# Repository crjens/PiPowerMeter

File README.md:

PiPowerMeter
=====

PiPowerMeter is an energy usage monitor based on the Cirrus Logic CS5463/5490 energy IC's (http://www.cirrus.com/en/products/pro/detail/P1092.html) and a Raspberry Pi.  It consists of two custom designed stacking pcb's.  The control board houses the power supply, energy IC, voltage sensors and supporting electronics.  The input board houses 16 multiplexed current input channels that allow monitoring up to 16 different circuits via standard clamp-on ct's.  A single control board supports up to 8 stacked input boards for a total monitoring capacity of up to 128 circuits.
The system is controlled by a nodejs based program running on the Raspberry Pi and includes a self contained web based monitoring portal.  Energy data are stored locally on the Raspberry Pi in a sqlite database making the system 100% stand-alone with no requirement for additional hardware or external servers.

Features
--------
 - 100% stand alone system with no reliance on external hardware or servers
 - Ability to monitor up to 128 circuits via round-robin sampling
 - Uses simple off the shelf clamp-on current sensors
 - Highly accurate measurement of voltage, current, power usage and power factor based on CS5463/CS5490 energy IC
 - Raspberry Pi based control system
   * All data stored locally in sqlite database
   * Web based monitoring portal for viewing energy usage and configuration
   * Ability to receive text alerts for overloads or other events.

Screenshots
-----------
- [Main](https://raw.githubusercontent.com/crjens/PiPowerMeter/master/Documentation/main.png)
- [Daily](https://raw.githubusercontent.com/crjens/PiPowerMeter/master/Documentation/graph.png)
- [Instantaneous](https://raw.githubusercontent.com/crjens/PiPowerMeter/master/Documentation/instant.png)
- [Readings](https://raw.githubusercontent.com/crjens/PiPowerMeter/master/Documentation/readings.png)
- [Configuration](https://raw.githubusercontent.com/crjens/PiPowerMeter/master/Documentation/config.png)

Additional Images
-----------------
- [Installed System](https://raw.githubusercontent.com/crjens/PiPowerMeter/master/Documentation/DSC_0077.JPG)
- [Installed System 2](https://raw.githubusercontent.com/crjens/PiPowerMeter/master/Documentation/DSC_0078.JPG)
- [Sensors](https://raw.githubusercontent.com/crjens/PiPowerMeter/master/Documentation/DSC_0002.JPG)
- [Boards](https://raw.githubusercontent.com/crjens/PiPowerMeter/master/Documentation/DSC_0012.JPG)

Hardware Installation
---------------------
1. The Raspberry Pi mounts directly to the 40-pin header on the control board and is powered from the control board's universal power supply.  Do not attempt to power the Raspberry Pi via its micro usb port or it may be damaged.
2. The control board requires a direct connection to the AC power source that is being monitored.  This AC connection provides both the voltage reference for the energy calculations as well as the power source for the Raspberry Pi and supporting electronics.  The AC power source is connected via 5 pin terminal connector shown [here](https://raw.githubusercontent.com/crjens/PiPowerMeter/master/Documentation/ACIn.jpg) and supports 100-240VAC and 50/60Hz.  

	- For US 120/240V split phase connect Ground, Neutral, AC1 and AC2.
	- For 240V single phase connect Ground, Neutral and AC1.
	- For 3 phase connect Ground, Neutral, AC1, AC2 and AC3.
3. Current sensors are connected to the input board via standard 3.5mm (1/8") audio plugs.  They must be current-type sensors without built-in sense resistors and must produce a full scale output of less than 50mA.  YHDC produces a full line of split-core current sensors that are easy to use, inexpensive and readily available [online](https://www.ebay.com/sch/i.html?_from=R40&_trksid=m570.l1313&_nkw=yhdc+sct013+sct006+sct019&_sacat=0&LH_TitleDesc=0&_osacat=0&_odkw=yhdc+sct013+sctoo0+sct019&LH_TitleDesc=0). Popular models include:
	- [YHDC-006 (20A)](http://en.yhdc.com/product1311.html?productId=612)
	- [YHDC-013-000 (100A)](http://en.yhdc.com/product1311.html?productId=401)
	- [YHDC-019 (200A)](http://en.yhdc.com/product1311.html?productId=380)
4. Connect the current sensors so that the current polarity reads correctly, (+) for circuits that consume energy and (-) for circuits that produce energy.  Connecting a sensor backwards will not harm anything so if you're not sure which way it should face just pick a direction and then reverse it if the readings are opposite of what you expect. 
	- Current sensors measure the sum of the current passing through them so they should normally be connected to a single conductor.  If connected to a multi-conductor cable, the current flowing in the line and neutral conductors will cancel each other and the sensor will read zero current.
	- YHDC sensors connected to line conductors should be oriented so that the printing on the face of the sensor faces toward the source (there's also an arrow on most sensors that should point toward the source).  If the sensor is connected to the neutral the direction should be reversed.  
5. Once the sensors are installed you'll need to configure the software to enable them.  This is done in the configuration page by adding a new circuit for each sensor and setting the sensor type, board, circuit and voltage reference.
	- There are several preconfigured types for common YHDC sensors and you can add additional types under the configuration tab.  When creating new sensor types set the scale value to 0.05 * the turns ratio of the sensor.  (YHDC SCT-013 has a turns ratio of 2000:1 so scale factor is 0.05*2000=100)
	- Board should be set to the id of the current board that the sensor is plugged into (0-7).
	- Channel should be set to the id that the sensor is plugged into (0-15).
	- Set Voltage to the voltage reference for the circuit.  If you aren't sure you can take a look at the current and voltage waveforms on the circuit page and experiment until you find the voltage reference that most closely matches the phase of the current waveform.
	- SampleTime sets the amount of time in seconds that the input current and voltage are sampled for each calculation.  Decreasing the SampleTime allows faster sampling but may adversly affect the accuracy of the calculations.  Valid values are between 0.05 and 60 seconds.  
	- Incorrect software settings won't cause any damage so you can experiment until you get them right.

Software Installation
---------------------
1. Any of the full size Raspberry Pi models with the 40 pin header are supported including: V1 A+, V1 B+, V2, V3 B, V3 B+ and V4 B.  The additional memory and computing power of the V2/V3/V4 models is recommended.
2. Start with latest Raspbian image from https://www.raspberrypi.org/software/operating-systems/
	1. (verified with Raspberry PI OS Lite 2021-03-04)
	2. It's recommended that you use the Lite version because it's smaller and installs faster but you can use either.
3. login to Pi with Putty or other ssh client
	1. the latest versions of Raspbian have ssh disabled.  You can enable ssh via raspi-config or just create an empty file named 'ssh' in the boot partition of the sd card.
4. Install the PiPowerMeter software by running the following command (you must install with root privileges such as the built-in pi account):
	1. wget -O - https://raw.githubusercontent.com/crjens/PiPowerMeter/master/setup.sh | bash
5. run 'sudo raspi-config' 
	1. set locale and timezone under Localisation options
	2. expand filesystem under Advanced options
	3. change user password (optional)
	4. reboot when prompted after exiting raspi-config
6. Open your browser to http://<Your Raspberry Pi's IP Address>:3000

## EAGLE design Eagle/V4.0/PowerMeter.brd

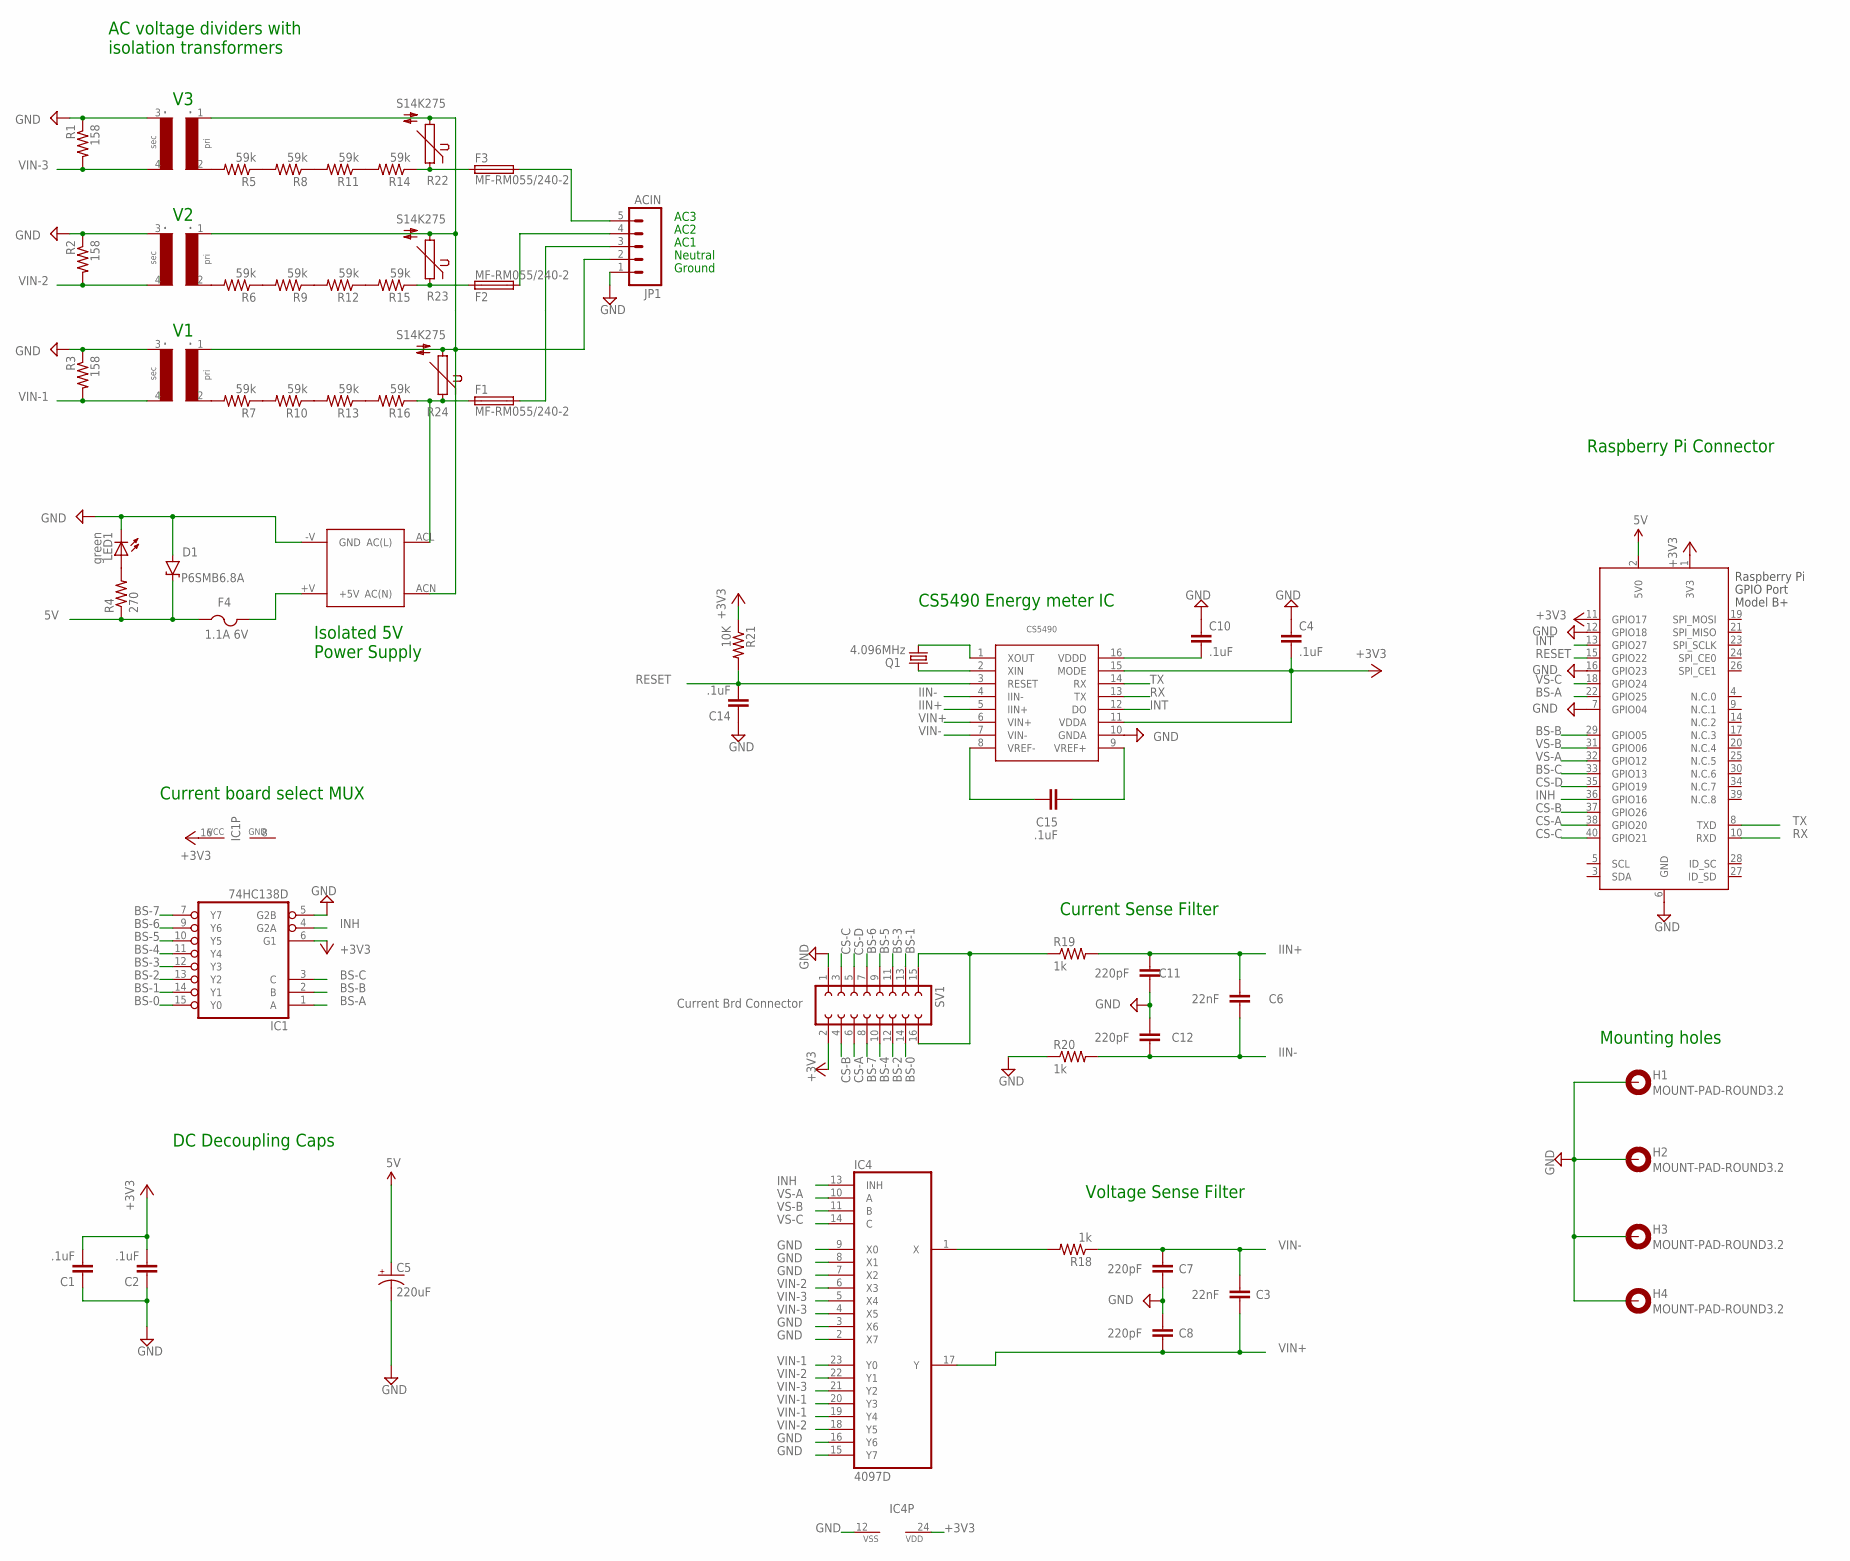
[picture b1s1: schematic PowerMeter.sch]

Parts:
C1, C2, C4, C10, C14, C15: .1uF; C1206; PARTNO C1206C104K5RAC7867
C3, C6: 22nF; C1206; PARTNO C1206C221J5GACTU
C5: 220uF; PANASONIC_D; PARTNO ESH227M016AE3AA
C7, C8, C11, C12: 220pF; C1206; PARTNO C1206C221J5GACTU
CS5490: CS5490; SOIC127P600X175-16N
D1: P6SMB6.8A; DO-214AA; PARTNO P6KE6.8A
F1, F2, F3: MF-RM055/240-2; TE5; PARTNO MF-RM055/240-2
F4: 1.1A 6V; 1812; PARTNO 0ZCC0110AF2C
H1, H2, H3, H4: MOUNT-PAD-ROUND3.2; 3,2-PAD
IC1: 74HC138D; SO16; PARTNO SN74HC138NSR
IC4: 4097D; SO24W
JP1: ACIN; SCREWTERMINAL-5MM-5; PARTNO 1935190
LED1: green; LED_1206; PARTNO LTST-C150GKT
Q1: 4.096MHz; HC49UP; PARTNO 9B-4.096MBBK-B
R1, R2, R3: 158; R1206; PARTNO RC1206FR-07158RL
R4: 270; R1206; PARTNO RC1206FR-07270RL
R5, R6, R7, R8, R9, R10, R11, R12, R13, R14, R15, R16: 59k; R1206; PARTNO RC1206FR-071KL
R18, R19, R20: 1k; R1206; PARTNO RC1206FR-071KL
R21: 10K; R1206; PARTNO RC1206FR-0710KL
R22, R23, R24: S14K275
SV1: Current Brd Connector; FE08-2; PARTNO PPTC082LFBN-RC
T1, T2, T3: TV16E
U$1: IRM-10
X1: RASPI_BOARD_B+_E4; RASPI_BOARD_B+_EDGES_4DRILL; PARTNO M20-9762046

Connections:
5V: C5.+, D1.C, F4.1, R4.1, X1.2 (5V0)
+3V3: C1.2, C2.2, C4.2, CS5490.11 (VDDA), CS5490.15 (MODE), IC1.6 (G1), IC1.16 (VCC), IC4.24 (VDD), R21.1, SV1.2, X1.1 (3V3), X1.11 (GPIO17)
+5V: F4.2, U$1.+V (+5V)
AC(L): F1.1, R16.1, R24.1, U$1.ACL (AC(L))
AC(N): JP1.2 (4), R22.2, R23.2, R24.2, T1.1, T2.1, T3.1, U$1.ACN (AC(N))
BS-0: IC1.15 (Y0), SV1.14
BS-1: IC1.14 (Y1), SV1.13
BS-2: IC1.13 (Y2), SV1.12
BS-3: IC1.12 (Y3), SV1.11
BS-4: IC1.11 (Y4), SV1.10
BS-5: IC1.10 (Y5), SV1.9
BS-6: IC1.9 (Y6), SV1.7
BS-7: IC1.7 (Y7), SV1.8
BS-A: IC1.1 (A), X1.22 (GPIO25)
BS-B: IC1.2 (B), X1.29 (GPIO05)
BS-C: IC1.3 (C), X1.33 (GPIO13)
CS-A: SV1.6, X1.38 (GPIO20)
CS-B: SV1.4, X1.37 (GPIO26)
CS-C: SV1.3, X1.40 (GPIO21)
CS-D: SV1.5, X1.35 (GPIO19)
GND: C1.1, C2.1, C4.1, C5.-, C7.1, C8.2, C10.1, C11.1, C12.2, C14.1, CS5490.10 (GNDA), D1.A, H1.B3,2, H2.B3,2, H3.B3,2, H4.B3,2, IC1.5 (G2B), IC1.8 (GND), IC4.2 (X7), IC4.3 (X6), IC4.7 (X2), IC4.8 (X1), IC4.9 (X0), IC4.12 (VSS), IC4.15 (Y7), IC4.16 (Y6), JP1.1 (5), LED1.C, R1.1, R2.1, R3.1, R20.1, SV1.1, T1.3, T2.3, T3.3, U$1.-V (GND), X1.6 (GND), X1.7 (GPIO04), X1.12 (GPIO18), X1.16 (GPIO23)
IIN+: C6.2, C11.2, CS5490.5 (IIN+), R19.2
IIN-: C6.1, C12.1, CS5490.4 (IIN-), R20.2
INH: IC1.4 (G2A), IC4.13 (INH), X1.36 (GPIO16)
INT: CS5490.12 (DO), X1.13 (GPIO27)
unnamed: CS5490.2 (XIN), Q1.1
unnamed: F2.1, R15.1, R23.1
unnamed: R5.1, R8.2
unnamed: R8.1, R11.2
unnamed: F1.2, JP1.3
unnamed: R9.1, R12.2
unnamed: LED1.A, R4.2
unnamed: IC4.1 (X), R18.2
unnamed: F3.2, JP1.5 (1)
unnamed: R13.1, R16.2
unnamed: R7.2, T3.2
unnamed: CS5490.1 (XOUT), Q1.2
unnamed: R7.1, R10.2
unnamed: R10.1, R13.2
unnamed: R6.2, T2.2
unnamed: R6.1, R9.2
unnamed: C10.2, CS5490.16 (VDDD)
unnamed: R12.1, R15.2
unnamed: R5.2, T1.2
unnamed: R11.1, R14.2
unnamed: F3.1, R14.1, R22.1
unnamed: R19.1, SV1.15, SV1.16
unnamed: C15.1, CS5490.8 (VREF-)
unnamed: C15.2, CS5490.9 (VREF+)
unnamed: F2.2, JP1.4 (2)
RESET: C14.2, CS5490.3 (RESET), R21.2, X1.15 (GPIO22)
RX: CS5490.13 (TX), X1.10 (RXD)
TX: CS5490.14 (RX), X1.8 (TXD)
VIN+: C3.1, C8.1, CS5490.6 (VIN+), IC4.17 (Y)
VIN-: C3.2, C7.2, CS5490.7 (VIN-), R18.1
VIN-1: IC4.19 (Y4), IC4.20 (Y3), IC4.23 (Y0), R3.2, T3.4
VIN-2: IC4.6 (X3), IC4.18 (Y5), IC4.22 (Y1), R2.2, T2.4
VIN-3: IC4.4 (X5), IC4.5 (X4), IC4.21 (Y2), R1.2, T1.4
VS-A: IC4.10 (A), X1.32 (GPIO12)
VS-B: IC4.11 (B), X1.31 (GPIO06)
VS-C: IC4.14 (C), X1.18 (GPIO24)

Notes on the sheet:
AC voltage dividers with isolation transformers
Isolated 5V Power Supply
DC Decoupling Caps
Raspberry Pi Connector
CS5490 Energy meter IC
Voltage Sense Filter
Current Sense Filter
Current board select MUX
Mounting holes
AC1
AC2
AC3
Neutral
Ground

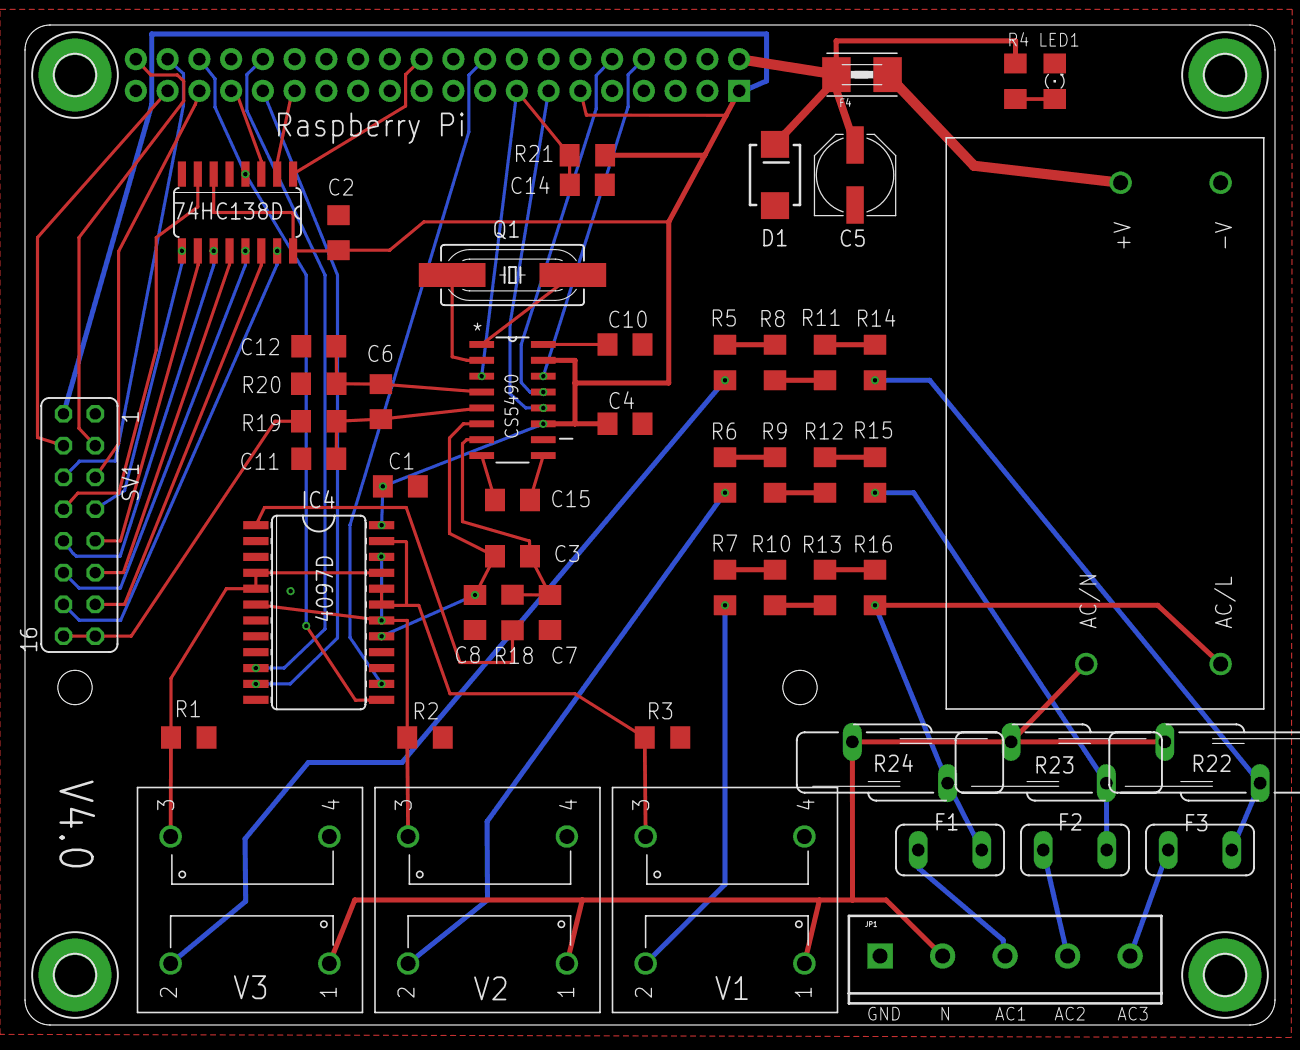
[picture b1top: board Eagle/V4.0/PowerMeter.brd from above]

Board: 2 copper layers, 100.0 x 80.0 mm, 57 parts (1 on the bottom side), 61 nets.

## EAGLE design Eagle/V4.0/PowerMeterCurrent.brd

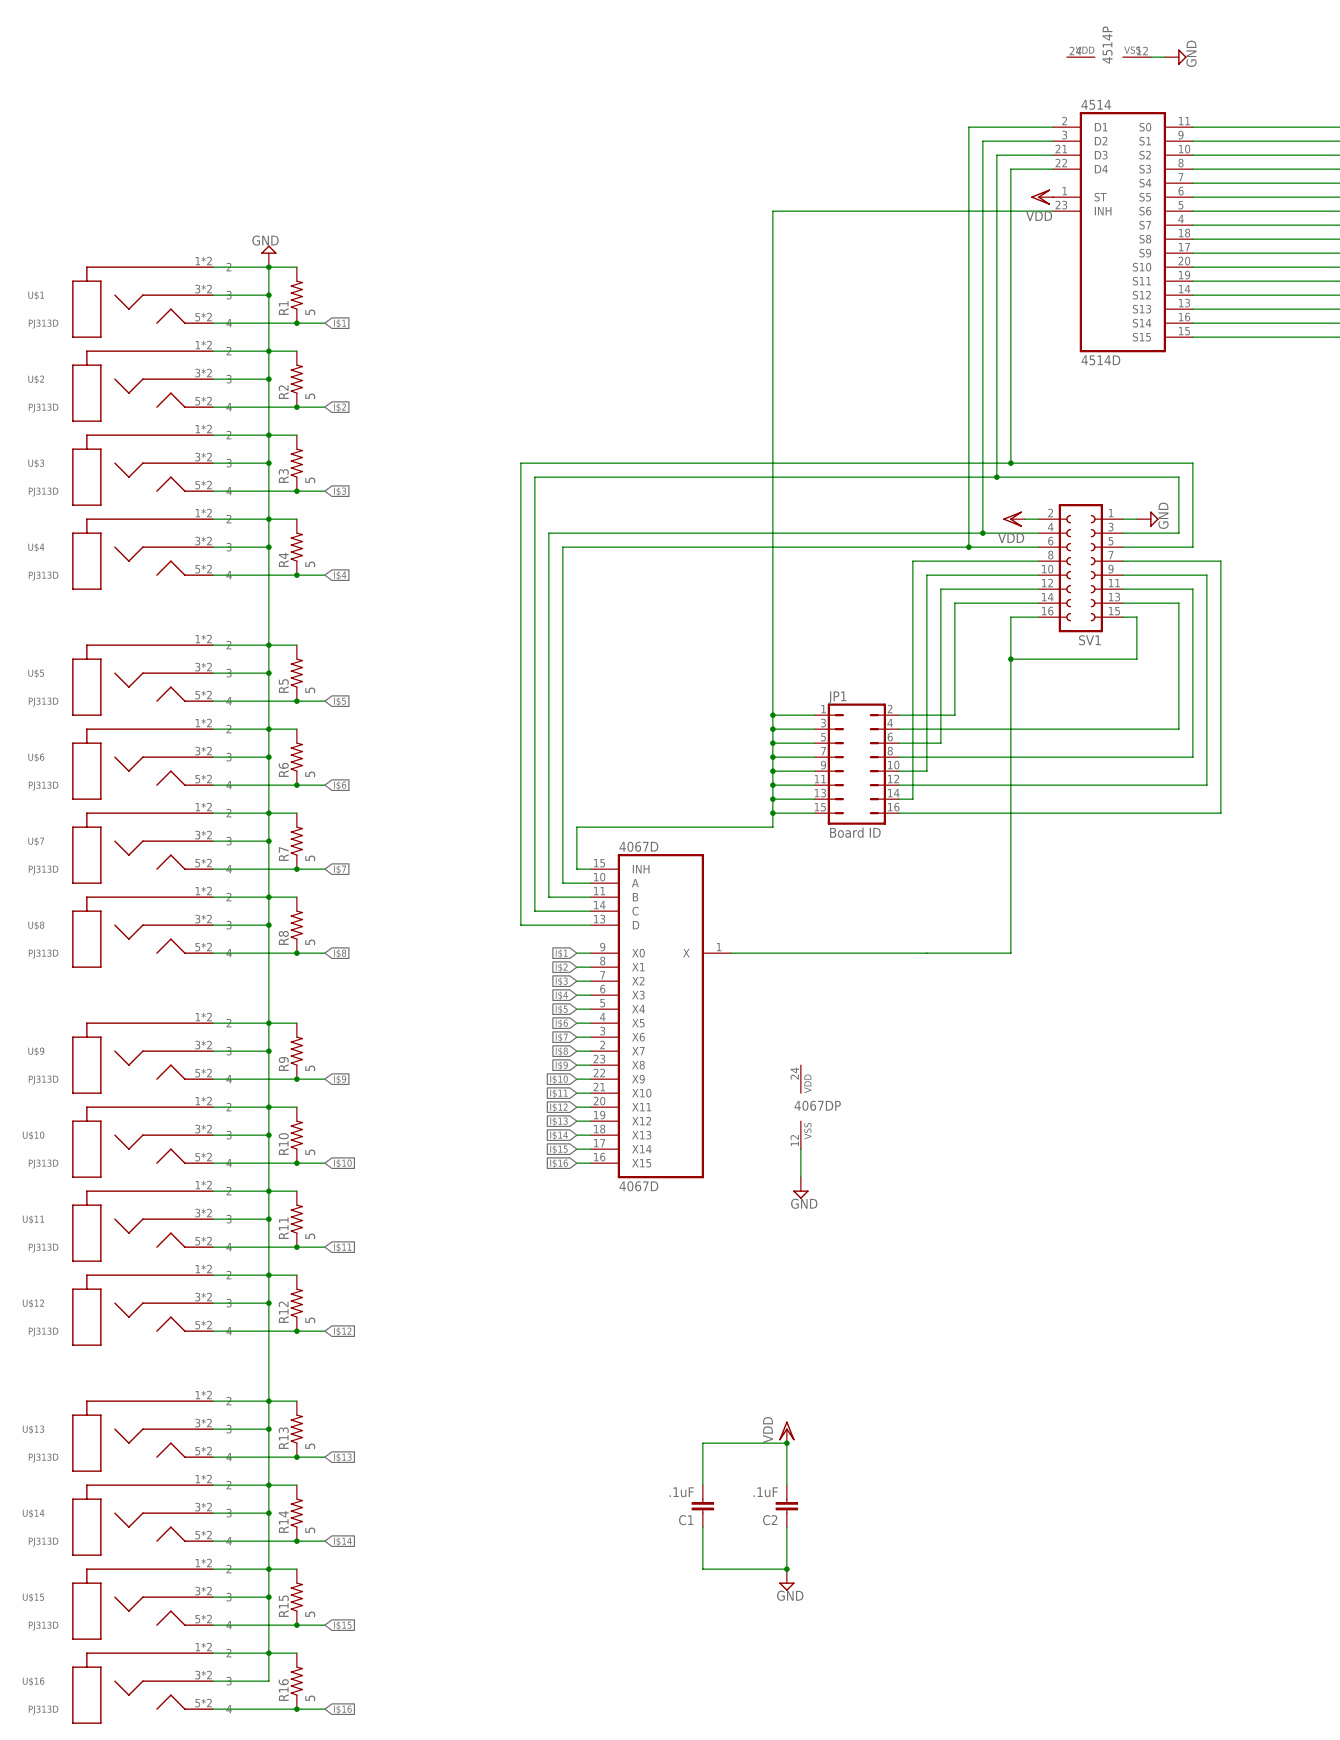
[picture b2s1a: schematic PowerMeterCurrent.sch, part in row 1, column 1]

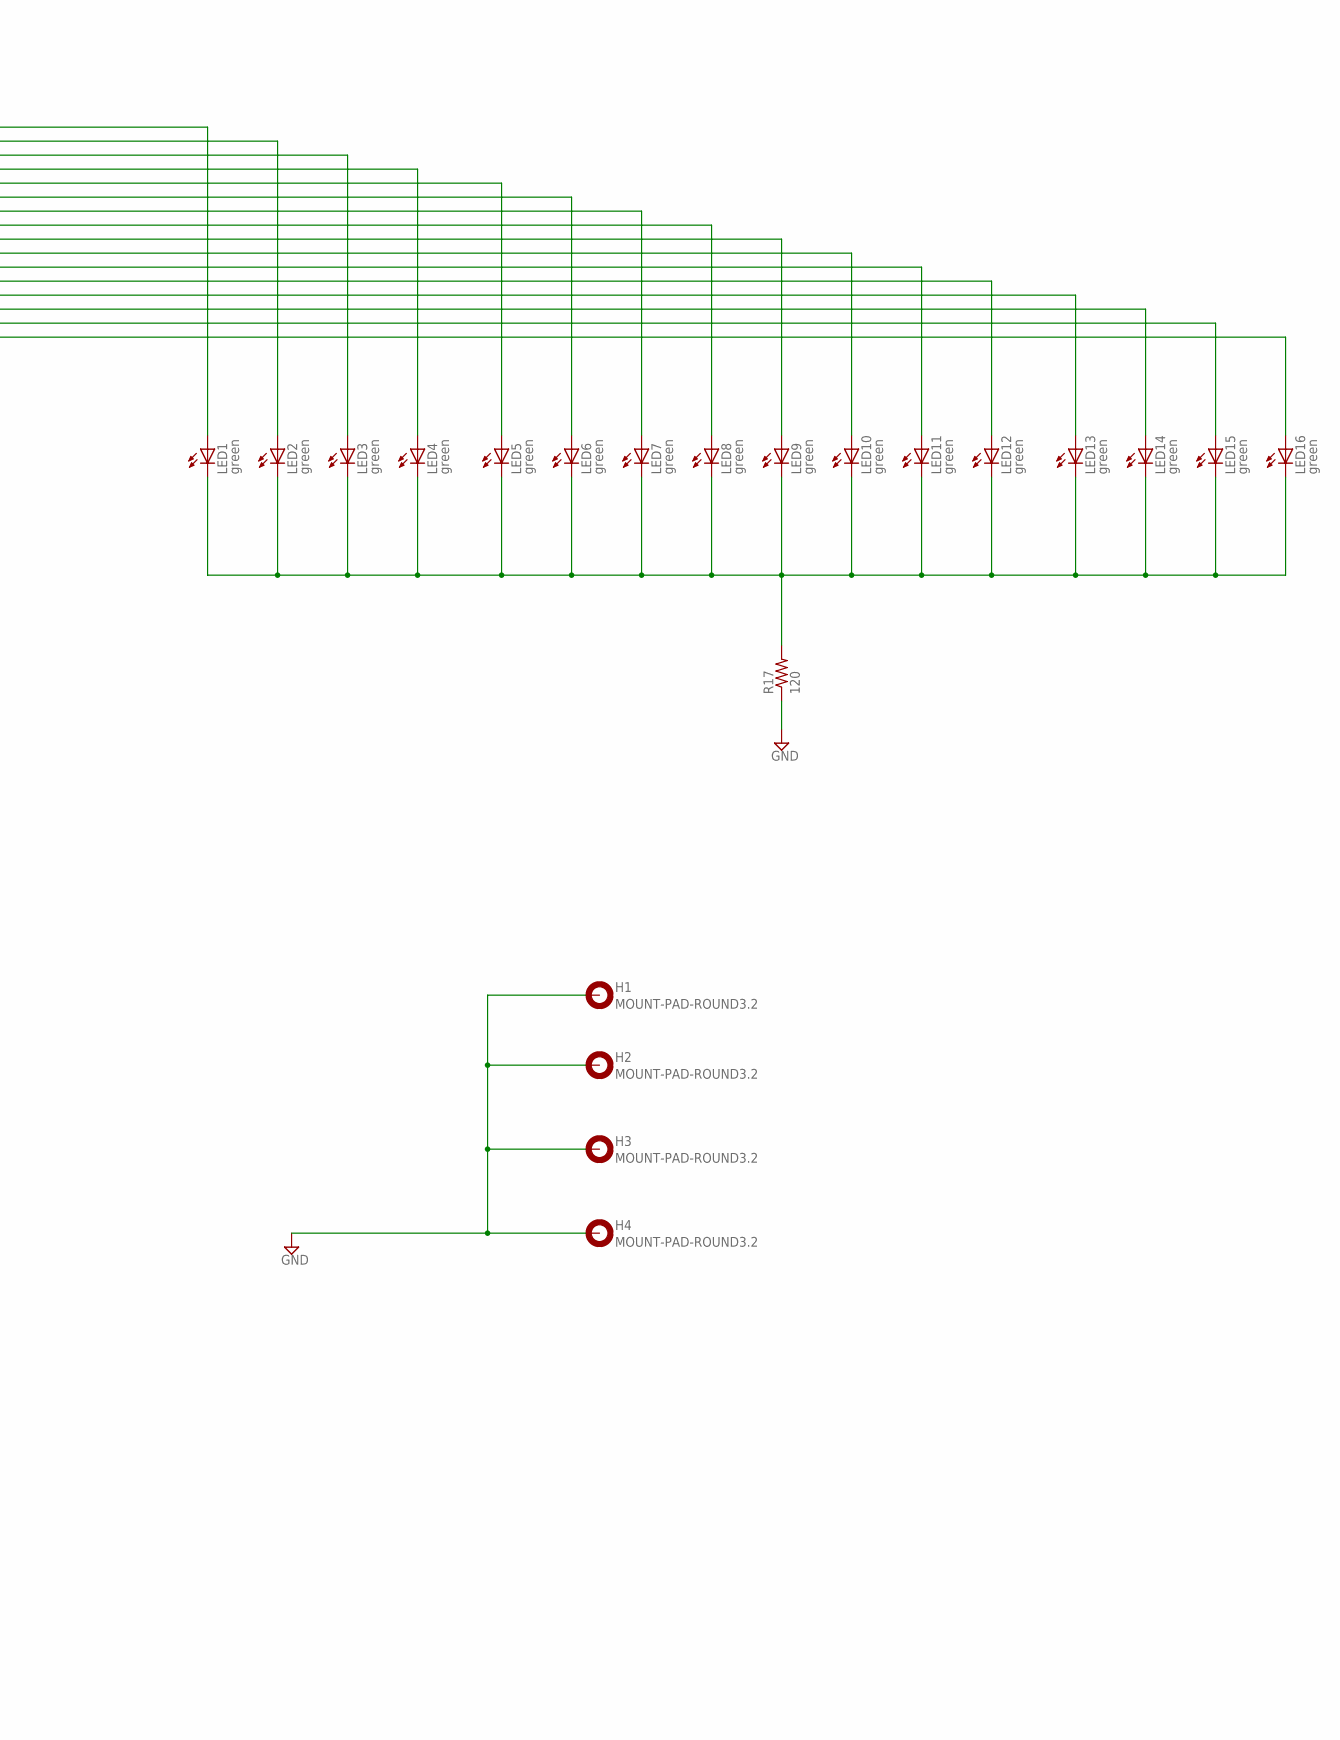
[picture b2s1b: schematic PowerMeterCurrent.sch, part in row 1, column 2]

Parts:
4067D: 4067D; SO24W; PARTNO 74HC4067D,652
4514: 4514D; SO24W; PARTNO 74HC154D,652
C1, C2: .1uF; C1206; PARTNO C1206C104K5RAC7867
H1, H2, H3, H4: MOUNT-PAD-ROUND3.2; 3,2-PAD
JP1: Board ID; JP8Q; PARTNO 67996-416HLF
LED1, LED2, LED3, LED4, LED5, LED6, LED7, LED8, LED9, LED10, LED11, LED12, LED13, LED14, LED15, LED16: green; LED_1206; PARTNO LTST-C150GKT
R1, R2, R3, R4, R5, R6, R7, R8, R9, R10, R11, R12, R13, R14, R15, R16: 5; R1206; PARTNO RC1206FR-077R5L
R17: 120; R1206; PARTNO RC1206FR-07120RL
SV1: FE08-2; PARTNO SSQ-108-02-T-D
U$1, U$2, U$3, U$4, U$5, U$6, U$7, U$8, U$9, U$10, U$11, U$12, U$13, U$14, U$15, U$16: PJ313D

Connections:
GND: 4067D.12 (VSS), 4514.12 (VSS), C1.1, C2.1, H1.B3,2, H2.B3,2, H3.B3,2, H4.B3,2, R1.2, R2.2, R3.2, R4.2, R5.2, R6.2, R7.2, R8.2, R9.2, R10.2, R11.2, R12.2, R13.2, R14.2, R15.2, R16.2, R17.1, SV1.1, U$1.1 (2), U$1.2, U$1.3, U$1.4 (3), U$2.1 (2), U$2.2, U$2.3, U$2.4 (3), U$3.1 (2), U$3.2, U$3.3, U$3.4 (3), U$4.1 (2), U$4.2, U$4.3, U$4.4 (3), U$5.1 (2), U$5.2, U$5.3, U$5.4 (3), U$6.1 (2), U$6.2, U$6.3, U$6.4 (3), U$7.1 (2), U$7.2, U$7.3, U$7.4 (3), U$8.1 (2), U$8.2, U$8.3, U$8.4 (3), U$9.1 (2), U$9.2, U$9.3, U$9.4 (3), U$10.1 (2), U$10.2, U$10.3, U$10.4 (3), U$11.1 (2), U$11.2, U$11.3, U$11.4 (3), U$12.1 (2), U$12.2, U$12.3, U$12.4 (3), U$13.1 (2), U$13.2, U$13.3, U$13.4 (3), U$14.1 (2), U$14.2, U$14.3, U$14.4 (3), U$15.1 (2), U$15.2, U$15.3, U$15.4 (3), U$16.1 (2), U$16.2, U$16.3, U$16.4 (3)
I$1: 4067D.9 (X0), R1.1, U$1.5 (4), U$1.6 (4)
I$2: 4067D.8 (X1), R2.1, U$2.5 (4), U$2.6 (4)
I$3: 4067D.7 (X2), R3.1, U$3.5 (4), U$3.6 (4)
I$4: 4067D.6 (X3), R4.1, U$4.5 (4), U$4.6 (4)
I$5: 4067D.5 (X4), R5.1, U$5.5 (4), U$5.6 (4)
I$6: 4067D.4 (X5), R6.1, U$6.5 (4), U$6.6 (4)
I$7: 4067D.3 (X6), R7.1, U$7.5 (4), U$7.6 (4)
I$8: 4067D.2 (X7), R8.1, U$8.5 (4), U$8.6 (4)
I$9: 4067D.23 (X8), R9.1, U$9.5 (4), U$9.6 (4)
I$10: 4067D.22 (X9), R10.1, U$10.5 (4), U$10.6 (4)
I$11: 4067D.21 (X10), R11.1, U$11.5 (4), U$11.6 (4)
I$12: 4067D.20 (X11), R12.1, U$12.5 (4), U$12.6 (4)
I$13: 4067D.19 (X12), R13.1, U$13.5 (4), U$13.6 (4)
I$14: 4067D.18 (X13), R14.1, U$14.5 (4), U$14.6 (4)
I$15: 4067D.17 (X14), R15.1, U$15.5 (4), U$15.6 (4)
I$16: 4067D.16 (X15), R16.1, U$16.5 (4), U$16.6 (4)
unnamed: 4067D.10 (A), 4514.2 (D1), SV1.6
unnamed: 4514.11 (S0), LED1.A
unnamed: 4067D.11 (B), 4514.3 (D2), SV1.4
unnamed: 4067D.14 (C), 4514.21 (D3), SV1.3
unnamed: 4067D.13 (D), 4514.22 (D4), SV1.5
unnamed: 4067D.15 (INH), 4514.23 (INH), JP1.1, JP1.3, JP1.5, JP1.7, JP1.9, JP1.11, JP1.13, JP1.15
unnamed: JP1.14, SV1.8
unnamed: JP1.10, SV1.10
unnamed: 4514.9 (S1), LED2.A
unnamed: JP1.6, SV1.12
unnamed: JP1.2, SV1.14
unnamed: 4067D.1 (X), SV1.15, SV1.16
unnamed: JP1.4, SV1.13
unnamed: JP1.8, SV1.11
unnamed: JP1.12, SV1.9
unnamed: JP1.16, SV1.7
unnamed: 4514.10 (S2), LED3.A
unnamed: LED1.C, LED2.C, LED3.C, LED4.C, LED5.C, LED6.C, LED7.C, LED8.C, LED9.C, LED10.C, LED11.C, LED12.C, LED13.C, LED14.C, LED15.C, LED16.C, R17.2
unnamed: 4514.8 (S3), LED4.A
unnamed: 4514.7 (S4), LED5.A
unnamed: 4514.6 (S5), LED6.A
unnamed: 4514.5 (S6), LED7.A
unnamed: 4514.4 (S7), LED8.A
unnamed: 4514.18 (S8), LED9.A
unnamed: 4514.17 (S9), LED10.A
unnamed: 4514.20 (S10), LED11.A
unnamed: 4514.19 (S11), LED12.A
unnamed: 4514.14 (S12), LED13.A
unnamed: 4514.13 (S13), LED14.A
unnamed: 4514.16 (S14), LED15.A
unnamed: 4514.15 (S15), LED16.A
VDD: 4067D.24 (VDD), 4514.1 (ST), 4514.24 (VDD), C1.2, C2.2, SV1.2

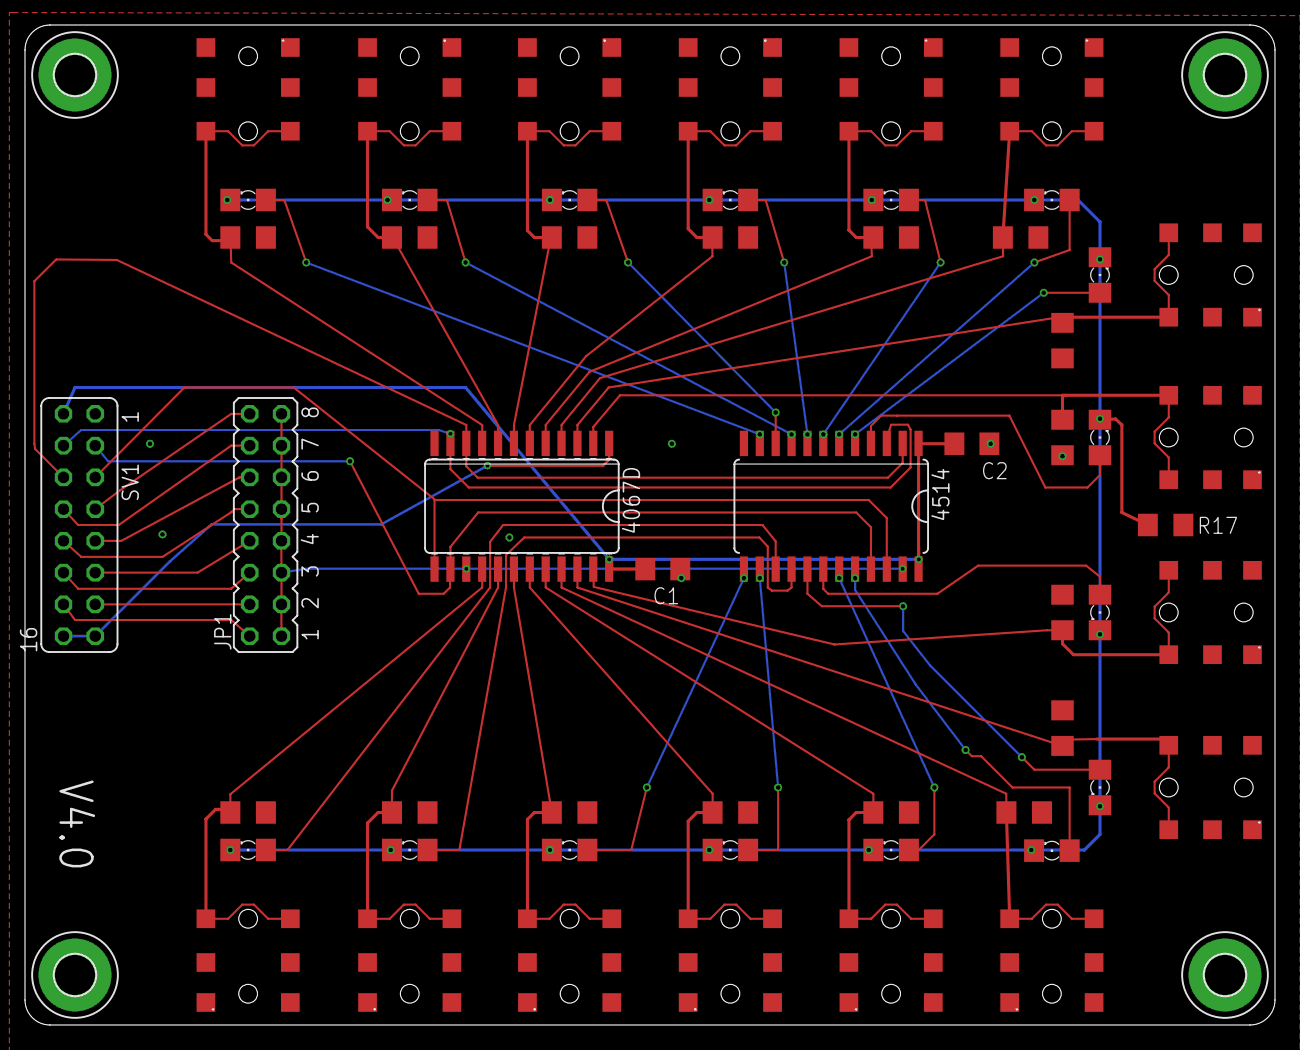
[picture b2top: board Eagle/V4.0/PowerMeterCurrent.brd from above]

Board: 2 copper layers, 100.0 x 80.0 mm, 59 parts (0 on the bottom side), 49 nets.

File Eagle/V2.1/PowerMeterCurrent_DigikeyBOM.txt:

Qty Value              Part Num           Package  Parts                                                                                                 Mfg Name           VID Vendor Part Num Description                      Pkg Code XREF 
1                      SSQ-108-02-T-D     FE08-2   SV1                                                                                                   Samtec Inc         DK  SAM1193-08-ND   CONN RCPT .100" 16POS DUAL TIN   REF33    *    
2   .1uF               C1206C104K5RAC7867 C1206    C1, C2                                                                                                Kemet              DK  399-1249-1-ND   CAP CER 0.1UF 50V 10% X7R 1206   1206     REF2 
16  5                  RC1206FR-075R1L    R1206    R1, R2, R3, R4, R5, R6, R7, R8, R9, R10, R11, R12, R13, R14, R15, R16                                 Yageo              DK  311-5.10FRCT-ND RES SMD 5.1 OHM 1% 1/4W 1206     1206     *    
1   120                RC1206FR-07120RL   R1206    R17                                                                                                   Yageo              DK  311-120FRCT-ND  RES SMD 120 OHM 1% 1/4W 1206     1206     REF12
1   4067D              74HC4067D,652      SO24W    IC1                                                                                                   NXP Semiconductors DK  568-2698-5-ND   IC MUX/DEMUX 1X16 24SOIC         REF31    *    
1   4514D              74HC154D,652       SO24W    IC2                                                                                                   NXP Semiconductors DK  568-1406-5-ND   IC DECODER/DEMUX 4-16LINE 24SOIC REF29    *    
1   Board ID           67996-416HLF       JP8Q     JP1                                                                                                   FCI                DK  609-3220-ND     CONN HEADER 16POS .100 STR TIN   REF30    *    
4   MOUNT-PAD-ROUND3.2 *                  3,2-PAD  H1, H2, H3, H4                                                                                        *                  *   *               *                                *        *    
16  STEREOJACK         SJ1-3525N          STX3100  X1, X2, X3, X4, X5, X6, X7, X8, X9, X10, X11, X12, X13, X14, X15, X16                                 CUI Inc            DK  CP1-3525N-ND    CONN JACK STEREO R/A 5PIN 3.5MM  REF32    *    
16  green              LTST-C150GKT       LED_1206 LED1, LED2, LED3, LED4, LED5, LED6, LED7, LED8, LED9, LED10, LED11, LED12, LED13, LED14, LED15, LED16 Lite-On Inc        DK  160-1169-1-ND   LED GREEN CLEAR 1206 SMD         1206     REF18

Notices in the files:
parts and their libraries:
SparkFun-Aesthetics: Licensing: Creative Commons ShareAlike 4.0 International - https://creativecommons.org/licenses/by-sa/4.0
